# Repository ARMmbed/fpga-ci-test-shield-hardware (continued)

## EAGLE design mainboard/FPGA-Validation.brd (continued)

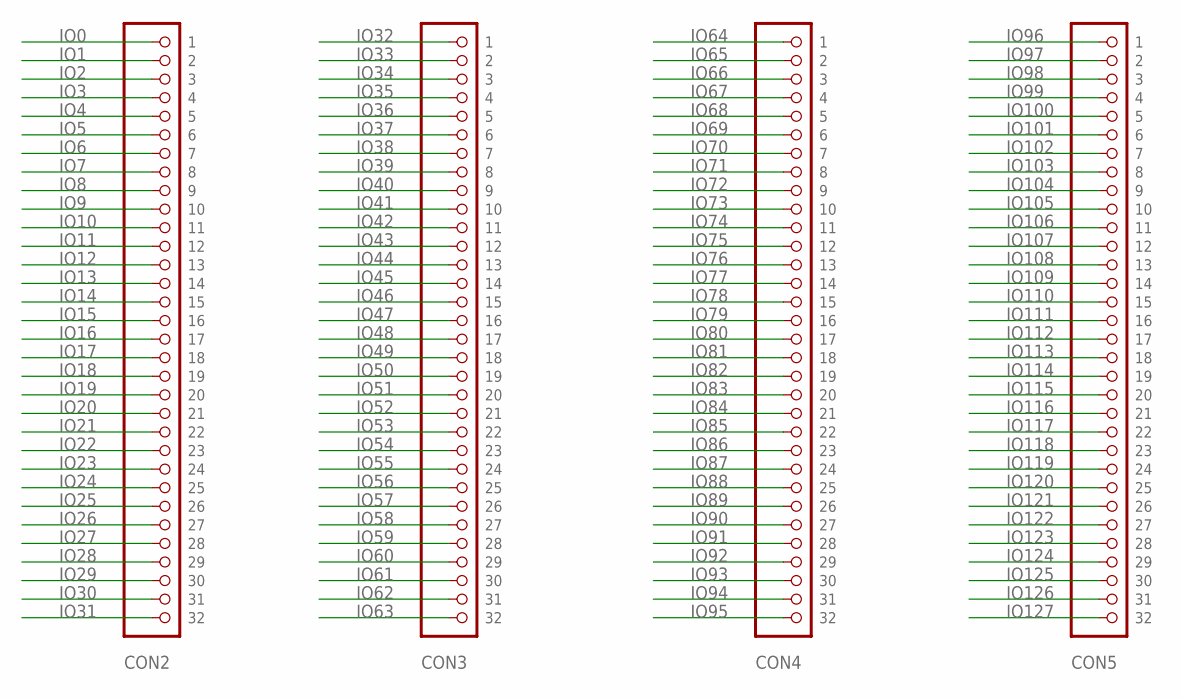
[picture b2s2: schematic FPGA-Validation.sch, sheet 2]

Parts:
CON2, CON3, CON4, CON5: PINHD-1X32; 1X32

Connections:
IO0: CON2.1; also elsewhere on the board
IO1: CON2.2; also elsewhere on the board
IO2: CON2.3; also elsewhere on the board
IO3: CON2.4; also elsewhere on the board
IO4: CON2.5; also elsewhere on the board
IO5: CON2.6; also elsewhere on the board
IO6: CON2.7; also elsewhere on the board
IO7: CON2.8; also elsewhere on the board
IO8: CON2.9; also elsewhere on the board
IO9: CON2.10; also elsewhere on the board
IO10: CON2.11; also elsewhere on the board
IO11: CON2.12; also elsewhere on the board
IO12: CON2.13; also elsewhere on the board
IO13: CON2.14; also elsewhere on the board
IO14: CON2.15; also elsewhere on the board
IO15: CON2.16; also elsewhere on the board
IO16: CON2.17; also elsewhere on the board
IO17: CON2.18; also elsewhere on the board
IO18: CON2.19; also elsewhere on the board
IO19: CON2.20; also elsewhere on the board
IO20: CON2.21; also elsewhere on the board
IO21: CON2.22; also elsewhere on the board
IO22: CON2.23; also elsewhere on the board
IO23: CON2.24; also elsewhere on the board
IO24: CON2.25; also elsewhere on the board
IO25: CON2.26; also elsewhere on the board
IO26: CON2.27; also elsewhere on the board
IO27: CON2.28; also elsewhere on the board
IO28: CON2.29; also elsewhere on the board
IO29: CON2.30; also elsewhere on the board
IO30: CON2.31; also elsewhere on the board
IO31: CON2.32; also elsewhere on the board
IO32: CON3.1; also elsewhere on the board
IO33: CON3.2; also elsewhere on the board
IO34: CON3.3; also elsewhere on the board
IO35: CON3.4; also elsewhere on the board
IO36: CON3.5; also elsewhere on the board
IO37: CON3.6; also elsewhere on the board
IO38: CON3.7; also elsewhere on the board
IO39: CON3.8; also elsewhere on the board
IO40: CON3.9; also elsewhere on the board
IO41: CON3.10; also elsewhere on the board
IO42: CON3.11; also elsewhere on the board
IO43: CON3.12; also elsewhere on the board
IO44: CON3.13; also elsewhere on the board
IO45: CON3.14; also elsewhere on the board
IO46: CON3.15; also elsewhere on the board
IO47: CON3.16; also elsewhere on the board
IO48: CON3.17; also elsewhere on the board
IO49: CON3.18; also elsewhere on the board
IO50: CON3.19; also elsewhere on the board
IO51: CON3.20; also elsewhere on the board
IO52: CON3.21; also elsewhere on the board
IO53: CON3.22; also elsewhere on the board
IO54: CON3.23; also elsewhere on the board
IO55: CON3.24; also elsewhere on the board
IO56: CON3.25; also elsewhere on the board
IO57: CON3.26; also elsewhere on the board
IO58: CON3.27; also elsewhere on the board
IO59: CON3.28; also elsewhere on the board
IO60: CON3.29; also elsewhere on the board
IO61: CON3.30; also elsewhere on the board
IO62: CON3.31; also elsewhere on the board
IO63: CON3.32; also elsewhere on the board
IO64: CON4.1; also elsewhere on the board
IO65: CON4.2; also elsewhere on the board
IO66: CON4.3; also elsewhere on the board
IO67: CON4.4; also elsewhere on the board
IO68: CON4.5; also elsewhere on the board
IO69: CON4.6; also elsewhere on the board
IO70: CON4.7; also elsewhere on the board
IO71: CON4.8; also elsewhere on the board
IO72: CON4.9; also elsewhere on the board
IO73: CON4.10; also elsewhere on the board
IO74: CON4.11; also elsewhere on the board
IO75: CON4.12; also elsewhere on the board
IO76: CON4.13; also elsewhere on the board
IO77: CON4.14; also elsewhere on the board
IO78: CON4.15; also elsewhere on the board
IO79: CON4.16; also elsewhere on the board
IO80: CON4.17; also elsewhere on the board
IO81: CON4.18; also elsewhere on the board
IO82: CON4.19; also elsewhere on the board
IO83: CON4.20; also elsewhere on the board
IO84: CON4.21; also elsewhere on the board
IO85: CON4.22; also elsewhere on the board
IO86: CON4.23; also elsewhere on the board
IO87: CON4.24; also elsewhere on the board
IO88: CON4.25; also elsewhere on the board
IO89: CON4.26; also elsewhere on the board
IO90: CON4.27; also elsewhere on the board
IO91: CON4.28; also elsewhere on the board
IO92: CON4.29; also elsewhere on the board
IO93: CON4.30; also elsewhere on the board
IO94: CON4.31; also elsewhere on the board
IO95: CON4.32; also elsewhere on the board
IO96: CON5.1; also elsewhere on the board
IO97: CON5.2; also elsewhere on the board
IO98: CON5.3; also elsewhere on the board
IO99: CON5.4; also elsewhere on the board
IO100: CON5.5; also elsewhere on the board
IO101: CON5.6; also elsewhere on the board
IO102: CON5.7; also elsewhere on the board
IO103: CON5.8; also elsewhere on the board
IO104: CON5.9; also elsewhere on the board
IO105: CON5.10; also elsewhere on the board
IO106: CON5.11; also elsewhere on the board
IO107: CON5.12; also elsewhere on the board
IO108: CON5.13; also elsewhere on the board
IO109: CON5.14; also elsewhere on the board
IO110: CON5.15; also elsewhere on the board
IO111: CON5.16; also elsewhere on the board
IO112: CON5.17; also elsewhere on the board
IO113: CON5.18; also elsewhere on the board
IO114: CON5.19; also elsewhere on the board
IO115: CON5.20; also elsewhere on the board
IO116: CON5.21; also elsewhere on the board
IO117: CON5.22; also elsewhere on the board
IO118: CON5.23; also elsewhere on the board
IO119: CON5.24; also elsewhere on the board
IO120: CON5.25; also elsewhere on the board
IO121: CON5.26; also elsewhere on the board
IO122: CON5.27; also elsewhere on the board
IO123: CON5.28; also elsewhere on the board
IO124: CON5.29; also elsewhere on the board
IO125: CON5.30; also elsewhere on the board
IO126: CON5.31; also elsewhere on the board
IO127: CON5.32; also elsewhere on the board

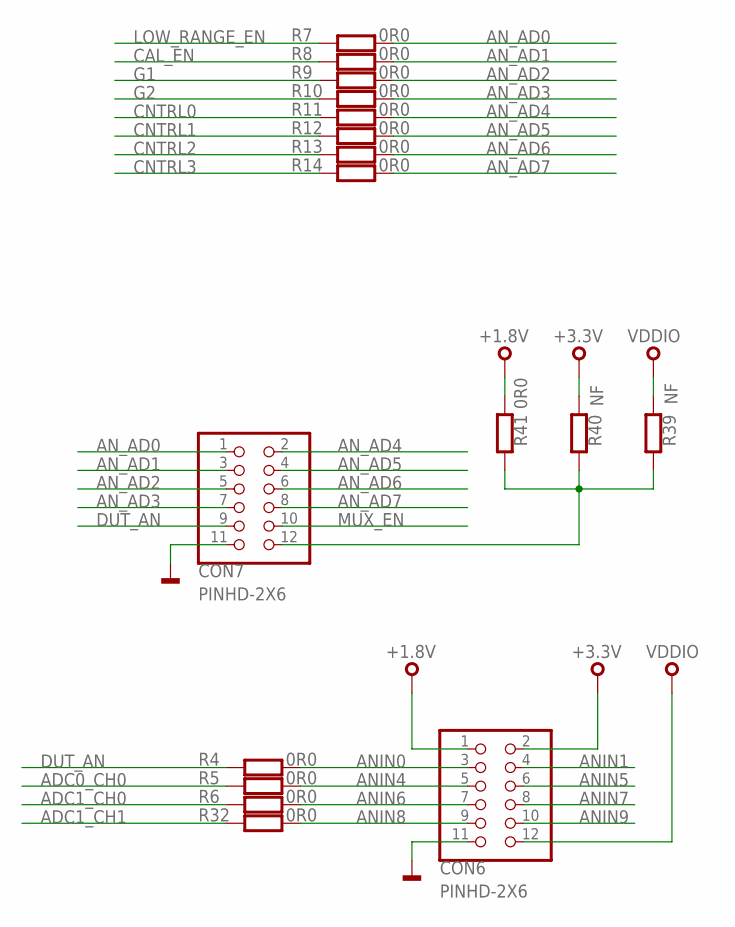
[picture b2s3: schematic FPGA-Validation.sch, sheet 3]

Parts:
CON6, CON7: PINHD-2X6; 2X06
R4, R5, R6, R7, R8, R9, R10, R11, R12, R13, R14, R32, R41: 0R0; 0603
R39, R40: NF; 0603

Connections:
+1.8V: CON6.1, R41.1; also elsewhere on the board
+3.3V: CON6.2, R40.1; also elsewhere on the board
ADC0_CH0: R5.1; also elsewhere on the board
ADC1_CH0: R6.1; also elsewhere on the board
ADC1_CH1: R32.1; also elsewhere on the board
ANIN0: CON6.3, R4.2; also elsewhere on the board
ANIN1: CON6.4; also elsewhere on the board
ANIN4: CON6.5, R5.2; also elsewhere on the board
ANIN5: CON6.6; also elsewhere on the board
ANIN6: CON6.7, R6.2; also elsewhere on the board
ANIN7: CON6.8; also elsewhere on the board
ANIN8: CON6.9, R32.2; also elsewhere on the board
ANIN9: CON6.10; also elsewhere on the board
AN_AD0: CON7.1, R7.2; also elsewhere on the board
AN_AD1: CON7.3, R8.2; also elsewhere on the board
AN_AD2: CON7.5, R9.2; also elsewhere on the board
AN_AD3: CON7.7, R10.2; also elsewhere on the board
AN_AD4: CON7.2, R11.2; also elsewhere on the board
AN_AD5: CON7.4, R12.2; also elsewhere on the board
AN_AD6: CON7.6, R13.2; also elsewhere on the board
AN_AD7: CON7.8, R14.2; also elsewhere on the board
CAL_EN: R8.1; also elsewhere on the board
CNTRL0: R11.1; also elsewhere on the board
CNTRL1: R12.1; also elsewhere on the board
CNTRL2: R13.1; also elsewhere on the board
CNTRL3: R14.1; also elsewhere on the board
DUT_AN: CON7.9, R4.1; also elsewhere on the board
G1: R9.1; also elsewhere on the board
G2: R10.1; also elsewhere on the board
GND: CON6.11, CON7.11; also elsewhere on the board
LOW_RANGE_EN: R7.1; also elsewhere on the board
MUX_EN: CON7.10; also elsewhere on the board
unnamed: CON7.12, R39.2, R40.2, R41.2
VDDIO: CON6.12, R39.1; also elsewhere on the board

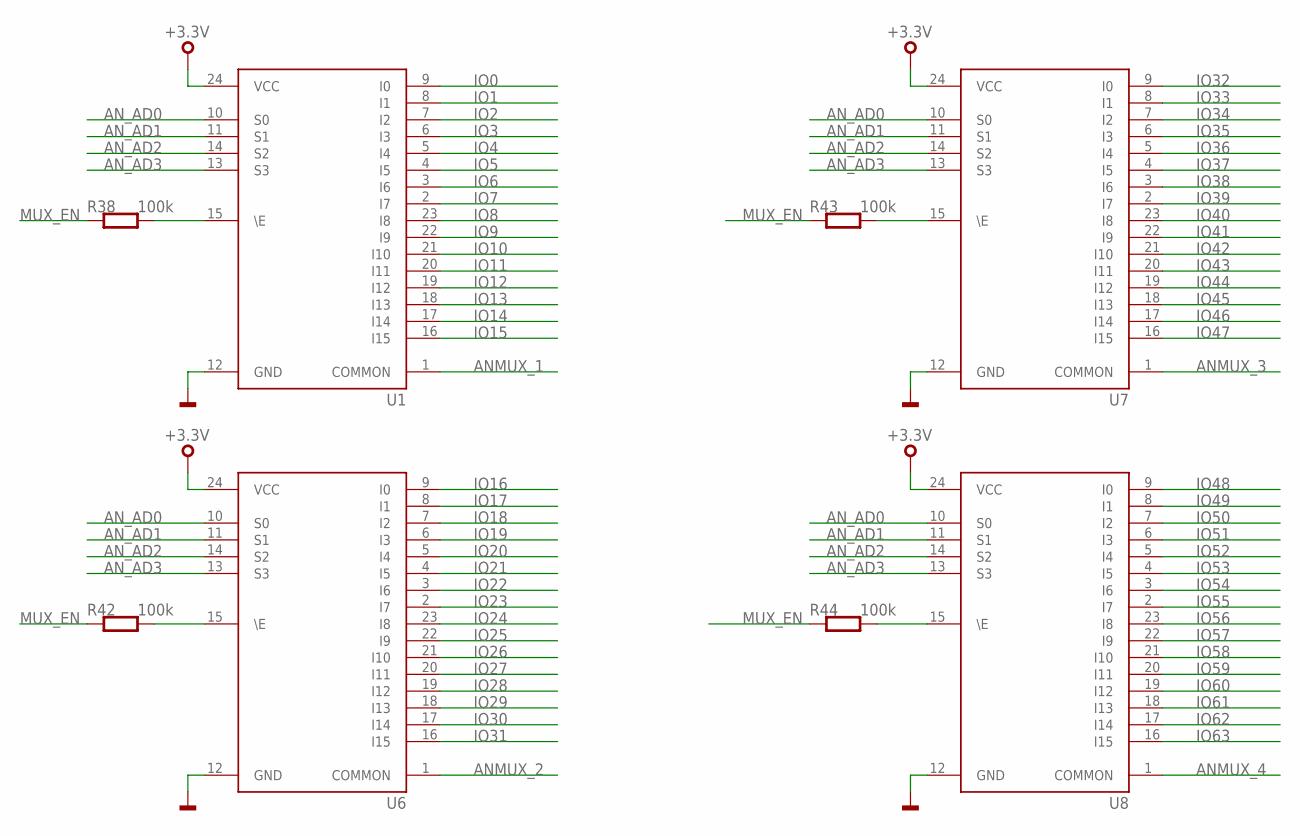
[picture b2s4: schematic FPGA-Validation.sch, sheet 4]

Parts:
R38, R42, R43, R44: 100k; 0603
U1, U6, U7, U8: CD74HCT4067; SO24

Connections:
+3.3V: U1.24 (VCC), U6.24 (VCC), U7.24 (VCC), U8.24 (VCC); also elsewhere on the board
ANMUX_1: U1.1 (COMMON); also elsewhere on the board
ANMUX_2: U6.1 (COMMON); also elsewhere on the board
ANMUX_3: U7.1 (COMMON); also elsewhere on the board
ANMUX_4: U8.1 (COMMON); also elsewhere on the board
AN_AD0: U1.10 (S0), U6.10 (S0), U7.10 (S0), U8.10 (S0); also elsewhere on the board
AN_AD1: U1.11 (S1), U6.11 (S1), U7.11 (S1), U8.11 (S1); also elsewhere on the board
AN_AD2: U1.14 (S2), U6.14 (S2), U7.14 (S2), U8.14 (S2); also elsewhere on the board
AN_AD3: U1.13 (S3), U6.13 (S3), U7.13 (S3), U8.13 (S3); also elsewhere on the board
GND: U1.12 (GND), U6.12 (GND), U7.12 (GND), U8.12 (GND); also elsewhere on the board
IO0: U1.9 (I0); also elsewhere on the board
IO1: U1.8 (I1); also elsewhere on the board
IO2: U1.7 (I2); also elsewhere on the board
IO3: U1.6 (I3); also elsewhere on the board
IO4: U1.5 (I4); also elsewhere on the board
IO5: U1.4 (I5); also elsewhere on the board
IO6: U1.3 (I6); also elsewhere on the board
IO7: U1.2 (I7); also elsewhere on the board
IO8: U1.23 (I8); also elsewhere on the board
IO9: U1.22 (I9); also elsewhere on the board
IO10: U1.21 (I10); also elsewhere on the board
IO11: U1.20 (I11); also elsewhere on the board
IO12: U1.19 (I12); also elsewhere on the board
IO13: U1.18 (I13); also elsewhere on the board
IO14: U1.17 (I14); also elsewhere on the board
IO15: U1.16 (I15); also elsewhere on the board
IO16: U6.9 (I0); also elsewhere on the board
IO17: U6.8 (I1); also elsewhere on the board
IO18: U6.7 (I2); also elsewhere on the board
IO19: U6.6 (I3); also elsewhere on the board
IO20: U6.5 (I4); also elsewhere on the board
IO21: U6.4 (I5); also elsewhere on the board
IO22: U6.3 (I6); also elsewhere on the board
IO23: U6.2 (I7); also elsewhere on the board
IO24: U6.23 (I8); also elsewhere on the board
IO25: U6.22 (I9); also elsewhere on the board
IO26: U6.21 (I10); also elsewhere on the board
IO27: U6.20 (I11); also elsewhere on the board
IO28: U6.19 (I12); also elsewhere on the board
IO29: U6.18 (I13); also elsewhere on the board
IO30: U6.17 (I14); also elsewhere on the board
IO31: U6.16 (I15); also elsewhere on the board
IO32: U7.9 (I0); also elsewhere on the board
IO33: U7.8 (I1); also elsewhere on the board
IO34: U7.7 (I2); also elsewhere on the board
IO35: U7.6 (I3); also elsewhere on the board
IO36: U7.5 (I4); also elsewhere on the board
IO37: U7.4 (I5); also elsewhere on the board
IO38: U7.3 (I6); also elsewhere on the board
IO39: U7.2 (I7); also elsewhere on the board
IO40: U7.23 (I8); also elsewhere on the board
IO41: U7.22 (I9); also elsewhere on the board
IO42: U7.21 (I10); also elsewhere on the board
IO43: U7.20 (I11); also elsewhere on the board
IO44: U7.19 (I12); also elsewhere on the board
IO45: U7.18 (I13); also elsewhere on the board
IO46: U7.17 (I14); also elsewhere on the board
IO47: U7.16 (I15); also elsewhere on the board
IO48: U8.9 (I0); also elsewhere on the board
IO49: U8.8 (I1); also elsewhere on the board
IO50: U8.7 (I2); also elsewhere on the board
IO51: U8.6 (I3); also elsewhere on the board
IO52: U8.5 (I4); also elsewhere on the board
IO53: U8.4 (I5); also elsewhere on the board
IO54: U8.3 (I6); also elsewhere on the board
IO55: U8.2 (I7); also elsewhere on the board
IO56: U8.23 (I8); also elsewhere on the board
IO57: U8.22 (I9); also elsewhere on the board
IO58: U8.21 (I10); also elsewhere on the board
IO59: U8.20 (I11); also elsewhere on the board
IO60: U8.19 (I12); also elsewhere on the board
IO61: U8.18 (I13); also elsewhere on the board
IO62: U8.17 (I14); also elsewhere on the board
IO63: U8.16 (I15); also elsewhere on the board
MUX_EN: R38.1, R42.1, R43.1, R44.1; also elsewhere on the board
unnamed: R42.2, U6.15 (\E)
unnamed: R43.2, U7.15 (\E)
unnamed: R38.2, U1.15 (\E)
unnamed: R44.2, U8.15 (\E)

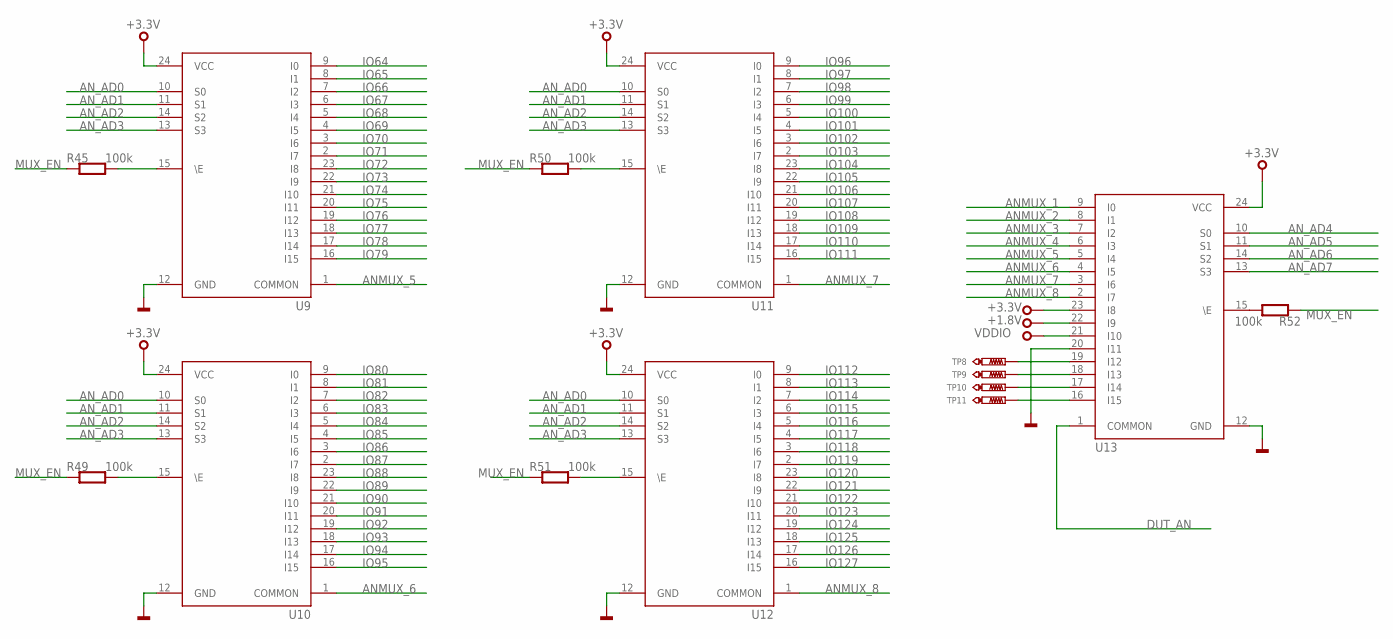
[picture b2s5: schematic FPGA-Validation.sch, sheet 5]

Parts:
R45, R49, R50, R51, R52: 100k; 0603
TP8, TP9, TP10, TP11: TEST_POINT-50R-PTH; TP50-PTH
U9, U10, U11, U12, U13: CD74HCT4067; SO24

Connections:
+1.8V: U13.22 (I9); also elsewhere on the board
+3.3V: U9.24 (VCC), U10.24 (VCC), U11.24 (VCC), U12.24 (VCC), U13.23 (I8), U13.24 (VCC); also elsewhere on the board
ANMUX_1: U13.9 (I0); also elsewhere on the board
ANMUX_2: U13.8 (I1); also elsewhere on the board
ANMUX_3: U13.7 (I2); also elsewhere on the board
ANMUX_4: U13.6 (I3); also elsewhere on the board
ANMUX_5: U9.1 (COMMON), U13.5 (I4)
ANMUX_6: U10.1 (COMMON), U13.4 (I5)
ANMUX_7: U11.1 (COMMON), U13.3 (I6)
ANMUX_8: U12.1 (COMMON), U13.2 (I7)
AN_AD0: U9.10 (S0), U10.10 (S0), U11.10 (S0), U12.10 (S0); also elsewhere on the board
AN_AD1: U9.11 (S1), U10.11 (S1), U11.11 (S1), U12.11 (S1); also elsewhere on the board
AN_AD2: U9.14 (S2), U10.14 (S2), U11.14 (S2), U12.14 (S2); also elsewhere on the board
AN_AD3: U9.13 (S3), U10.13 (S3), U11.13 (S3), U12.13 (S3); also elsewhere on the board
AN_AD4: U13.10 (S0); also elsewhere on the board
AN_AD5: U13.11 (S1); also elsewhere on the board
AN_AD6: U13.14 (S2); also elsewhere on the board
AN_AD7: U13.13 (S3); also elsewhere on the board
DUT_AN: U13.1 (COMMON); also elsewhere on the board
GND: U9.12 (GND), U10.12 (GND), U11.12 (GND), U12.12 (GND), U13.12 (GND), U13.20 (I11); also elsewhere on the board
IO64: U9.9 (I0); also elsewhere on the board
IO65: U9.8 (I1); also elsewhere on the board
IO66: U9.7 (I2); also elsewhere on the board
IO67: U9.6 (I3); also elsewhere on the board
IO68: U9.5 (I4); also elsewhere on the board
IO69: U9.4 (I5); also elsewhere on the board
IO70: U9.3 (I6); also elsewhere on the board
IO71: U9.2 (I7); also elsewhere on the board
IO72: U9.23 (I8); also elsewhere on the board
IO73: U9.22 (I9); also elsewhere on the board
IO74: U9.21 (I10); also elsewhere on the board
IO75: U9.20 (I11); also elsewhere on the board
IO76: U9.19 (I12); also elsewhere on the board
IO77: U9.18 (I13); also elsewhere on the board
IO78: U9.17 (I14); also elsewhere on the board
IO79: U9.16 (I15); also elsewhere on the board
IO80: U10.9 (I0); also elsewhere on the board
IO81: U10.8 (I1); also elsewhere on the board
IO82: U10.7 (I2); also elsewhere on the board
IO83: U10.6 (I3); also elsewhere on the board
IO84: U10.5 (I4); also elsewhere on the board
IO85: U10.4 (I5); also elsewhere on the board
IO86: U10.3 (I6); also elsewhere on the board
IO87: U10.2 (I7); also elsewhere on the board
IO88: U10.23 (I8); also elsewhere on the board
IO89: U10.22 (I9); also elsewhere on the board
IO90: U10.21 (I10); also elsewhere on the board
IO91: U10.20 (I11); also elsewhere on the board
IO92: U10.19 (I12); also elsewhere on the board
IO93: U10.18 (I13); also elsewhere on the board
IO94: U10.17 (I14); also elsewhere on the board
IO95: U10.16 (I15); also elsewhere on the board
IO96: U11.9 (I0); also elsewhere on the board
IO97: U11.8 (I1); also elsewhere on the board
IO98: U11.7 (I2); also elsewhere on the board
IO99: U11.6 (I3); also elsewhere on the board
IO100: U11.5 (I4); also elsewhere on the board
IO101: U11.4 (I5); also elsewhere on the board
IO102: U11.3 (I6); also elsewhere on the board
IO103: U11.2 (I7); also elsewhere on the board
IO104: U11.23 (I8); also elsewhere on the board
IO105: U11.22 (I9); also elsewhere on the board
IO106: U11.21 (I10); also elsewhere on the board
IO107: U11.20 (I11); also elsewhere on the board
IO108: U11.19 (I12); also elsewhere on the board
IO109: U11.18 (I13); also elsewhere on the board
IO110: U11.17 (I14); also elsewhere on the board
IO111: U11.16 (I15); also elsewhere on the board
IO112: U12.9 (I0); also elsewhere on the board
IO113: U12.8 (I1); also elsewhere on the board
IO114: U12.7 (I2); also elsewhere on the board
IO115: U12.6 (I3); also elsewhere on the board
IO116: U12.5 (I4); also elsewhere on the board
IO117: U12.4 (I5); also elsewhere on the board
IO118: U12.3 (I6); also elsewhere on the board
IO119: U12.2 (I7); also elsewhere on the board
IO120: U12.23 (I8); also elsewhere on the board
IO121: U12.22 (I9); also elsewhere on the board
IO122: U12.21 (I10); also elsewhere on the board
IO123: U12.20 (I11); also elsewhere on the board
IO124: U12.19 (I12); also elsewhere on the board
IO125: U12.18 (I13); also elsewhere on the board
IO126: U12.17 (I14); also elsewhere on the board
IO127: U12.16 (I15); also elsewhere on the board
MUX_EN: R45.1, R49.1, R50.1, R51.1, R52.1; also elsewhere on the board
unnamed: R45.2, U9.15 (\E)
unnamed: R49.2, U10.15 (\E)
unnamed: R50.2, U11.15 (\E)
unnamed: R51.2, U12.15 (\E)
unnamed: R52.2, U13.15 (\E)
unnamed: TP8.TP, U13.19 (I12)
unnamed: TP9.TP, U13.18 (I13)
unnamed: TP10.TP, U13.17 (I14)
unnamed: TP11.TP, U13.16 (I15)
VDDIO: U13.21 (I10); also elsewhere on the board

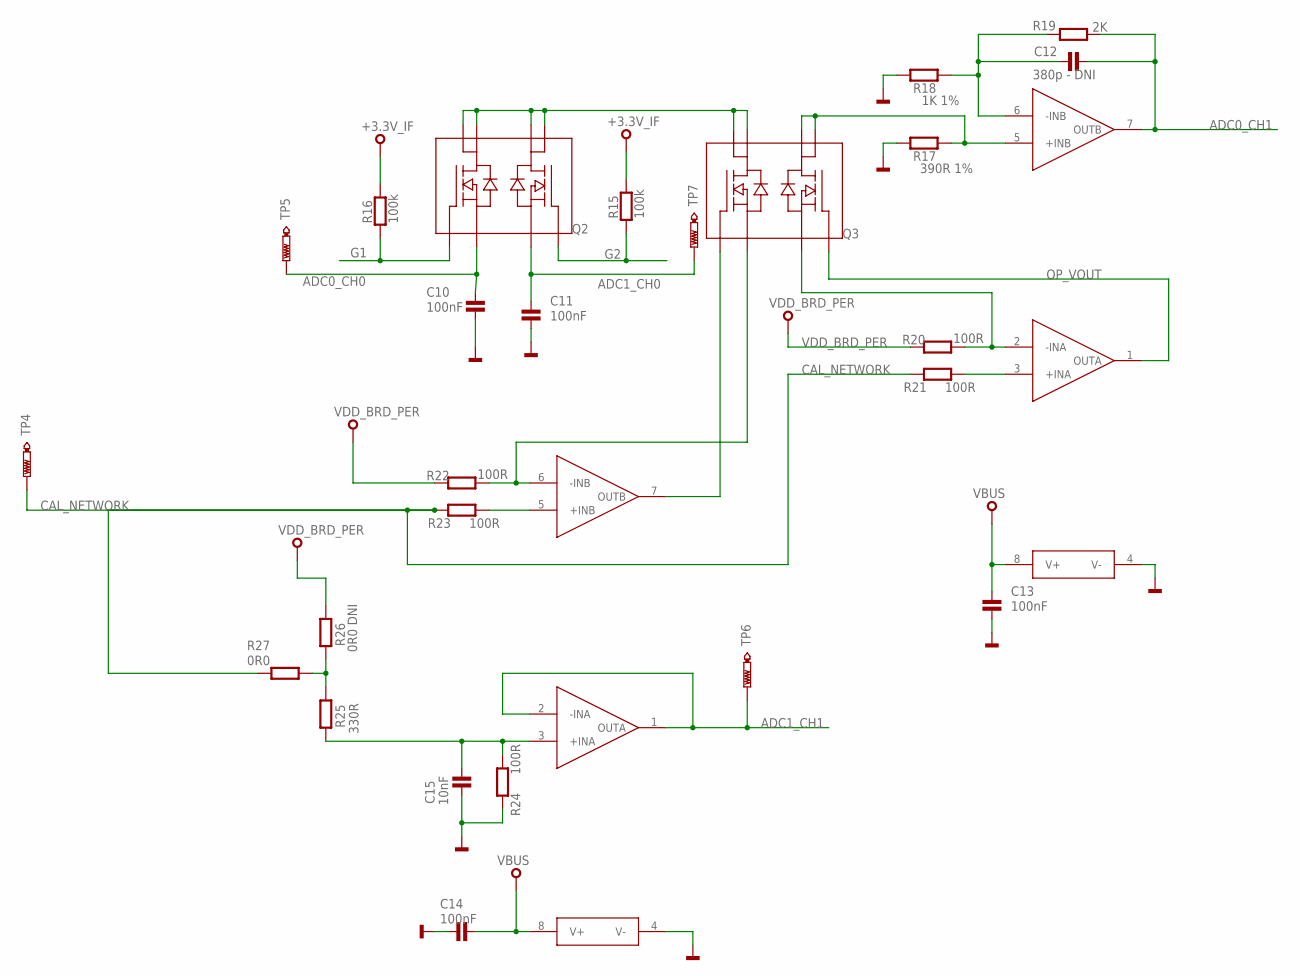
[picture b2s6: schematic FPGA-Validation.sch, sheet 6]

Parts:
C10, C11, C13, C14: 100nF; 0603
C12: 380p - DNI; 0603
C15: 10nF; 0603
Q2, Q3: PMDPB55XP; SOT1118
R15, R16: 100k; 0603@1
R17: 390R 1%; 0603@1
R18: 1K 1%; 0603@1
R19: 2K; 0603@1
R20, R21, R22, R23, R24: 100R; 0603@1
R25: 330R; 0603@1
R26: 0R0 DNI; 0603@1
R27: 0R0; 0603@1
TP4, TP5, TP6, TP7: TEST-POINT-50R-PTH; TP50-PTH
U2, U3: LTC2051IMS8; MSOP8

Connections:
+3.3V_IF: R15.2, R16.2
ADC0_CH0: C10.1, Q2.3 (D2A), TP5.TP; also elsewhere on the board
ADC0_CH1: C12.2, R19.1, U3.7 (OUTB)
ADC1_CH0: C11.1, Q2.7 (D1B), TP7.TP; also elsewhere on the board
ADC1_CH1: TP6.TP, U2.1 (OUTA), U2.2 (-INA); also elsewhere on the board
CAL_NETWORK: R21.2, R23.2, R27.1, TP4.TP; also elsewhere on the board
G1: Q2.8 (D2B), R16.1; also elsewhere on the board
G2: Q2.6 (D1A), R15.1; also elsewhere on the board
GND: C10.2, C11.2, C13.2, C14.2, C15.2, R17.2, R18.2, R24.2, U2.4 (V-), U3.4 (V-); also elsewhere on the board
unnamed: Q2.1 (S1), Q2.2 (G1), Q2.4 (S2), Q2.5 (G2), Q3.4 (S2), Q3.5 (G2)
unnamed: Q3.1 (S1), Q3.2 (G1), R17.1, U3.5 (+INB)
unnamed: C12.1, R18.1, R19.2, U3.6 (-INB)
unnamed: Q3.7 (D1B), R20.1, U3.2 (-INA)
unnamed: R21.1, U3.3 (+INA)
unnamed: Q3.3 (D2A), R22.1, U2.6 (-INB)
unnamed: R23.1, U2.5 (+INB)
unnamed: Q3.8 (D2B), U2.7 (OUTB)
unnamed: C15.1, R24.1, R25.2, U2.3 (+INA)
unnamed: R25.1, R26.2, R27.2
OP_VOUT: Q3.6 (D1A), U3.1 (OUTA)
VBUS: C13.1, C14.1, U2.8 (V+), U3.8 (V+)
VDD_BRD_PER: R20.2, R22.2, R26.1; also elsewhere on the board

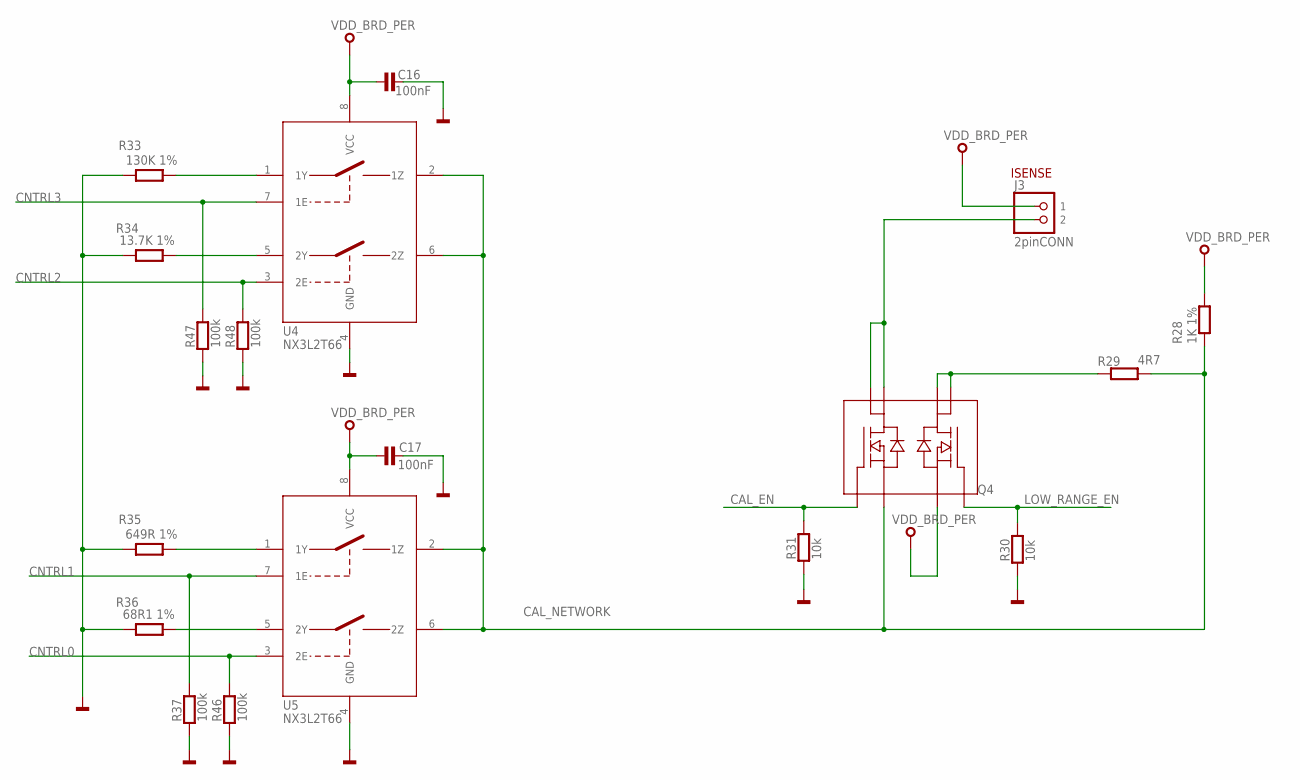
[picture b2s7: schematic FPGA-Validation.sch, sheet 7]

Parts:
C16, C17: 100nF; 0603
J3: 2pinCONN; 1X02
Q4: PMDPB55XP; SOT1118
R28: 1K 1%; 0603@1
R29: 4R7; 0603@1
R30, R31: 10k; 0603@1
R33: 130K 1%; 0603@1
R34: 13.7K 1%; 0603@1
R35: 649R 1%; 0603@1
R36: 68R1 1%; 0603@1
R37, R46, R47, R48: 100k; 0603@1
U4, U5: NX3L2T66; XSON8

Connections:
CAL_EN: Q4.8 (D2B), R31.2; also elsewhere on the board
CAL_NETWORK: Q4.3 (D2A), R28.1, R29.1, U4.2 (1Z), U4.6 (2Z), U5.2 (1Z), U5.6 (2Z); also elsewhere on the board
CNTRL0: R46.2, U5.3 (2E); also elsewhere on the board
CNTRL1: R37.2, U5.7 (1E); also elsewhere on the board
CNTRL2: R48.2, U4.3 (2E); also elsewhere on the board
CNTRL3: R47.2, U4.7 (1E); also elsewhere on the board
GND: C16.1, C17.1, R30.1, R31.1, R33.2, R34.2, R35.2, R36.2, R37.1, R46.1, R47.1, R48.1, U4.4 (GND), U5.4 (GND); also elsewhere on the board
LOW_RANGE_EN: Q4.6 (D1A), R30.2; also elsewhere on the board
unnamed: J3.2, Q4.4 (S2), Q4.5 (G2)
unnamed: Q4.1 (S1), Q4.2 (G1), R29.2
unnamed: R33.1, U4.1 (1Y)
unnamed: R34.1, U4.5 (2Y)
unnamed: R35.1, U5.1 (1Y)
unnamed: R36.1, U5.5 (2Y)
VDD_BRD_PER: C16.2, C17.2, J3.1, Q4.7 (D1B), R28.2, U4.8 (VCC), U5.8 (VCC); also elsewhere on the board

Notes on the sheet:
ISENSE

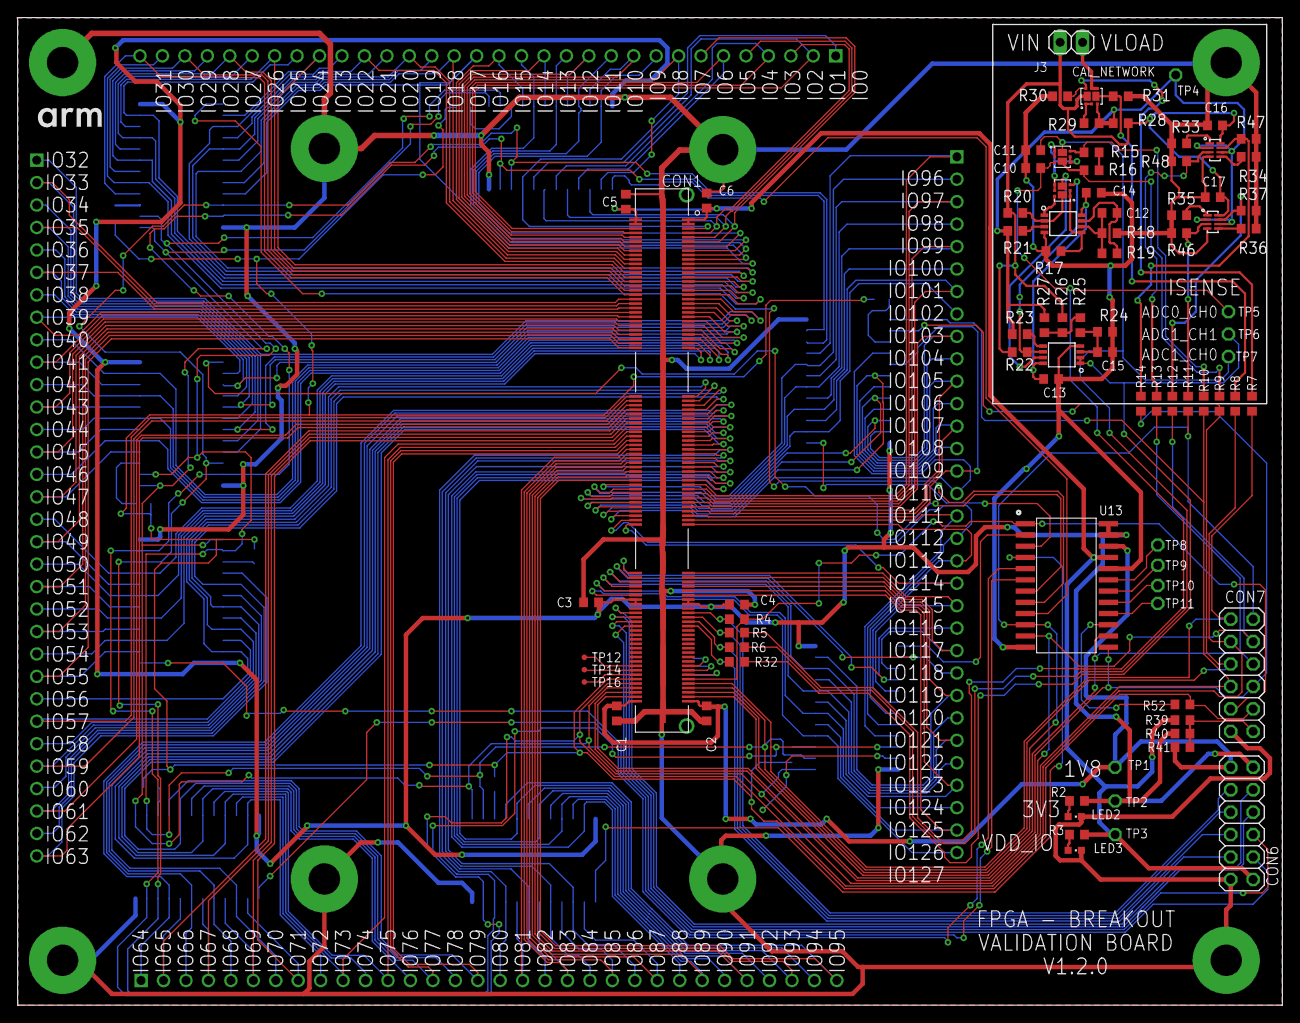
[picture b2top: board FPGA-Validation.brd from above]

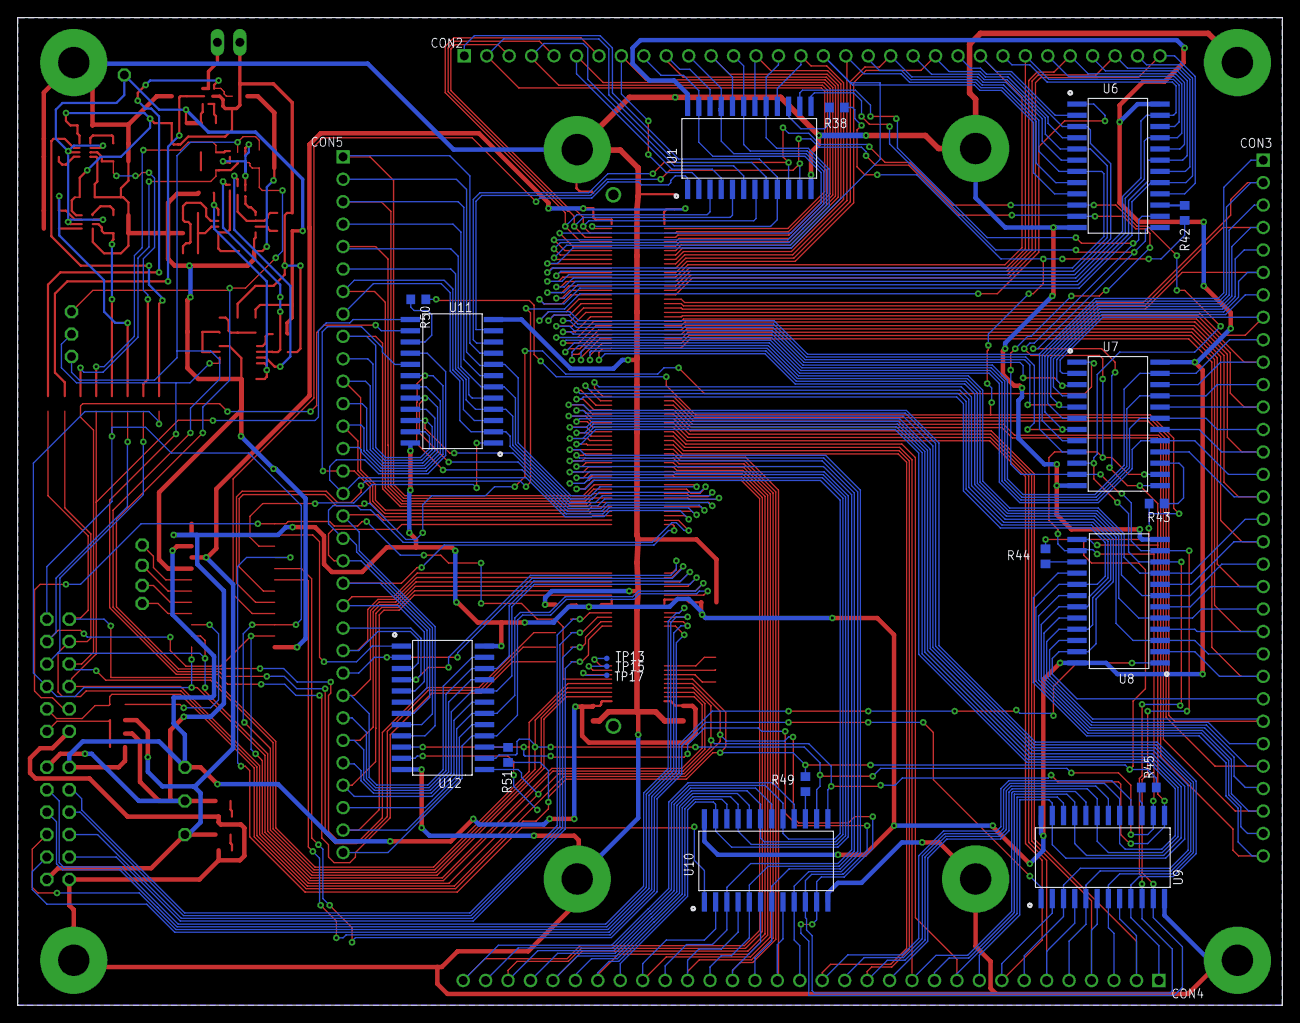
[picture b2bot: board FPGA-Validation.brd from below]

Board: 2 copper layers, 143.1 x 111.8 mm, 116 parts (19 on the bottom side), 213 nets.

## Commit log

2021-02-04 Add LICENSE file
2021-02-16 Tweak to align project with repo name
